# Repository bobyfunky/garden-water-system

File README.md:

# garden-water-system
Automatic water system

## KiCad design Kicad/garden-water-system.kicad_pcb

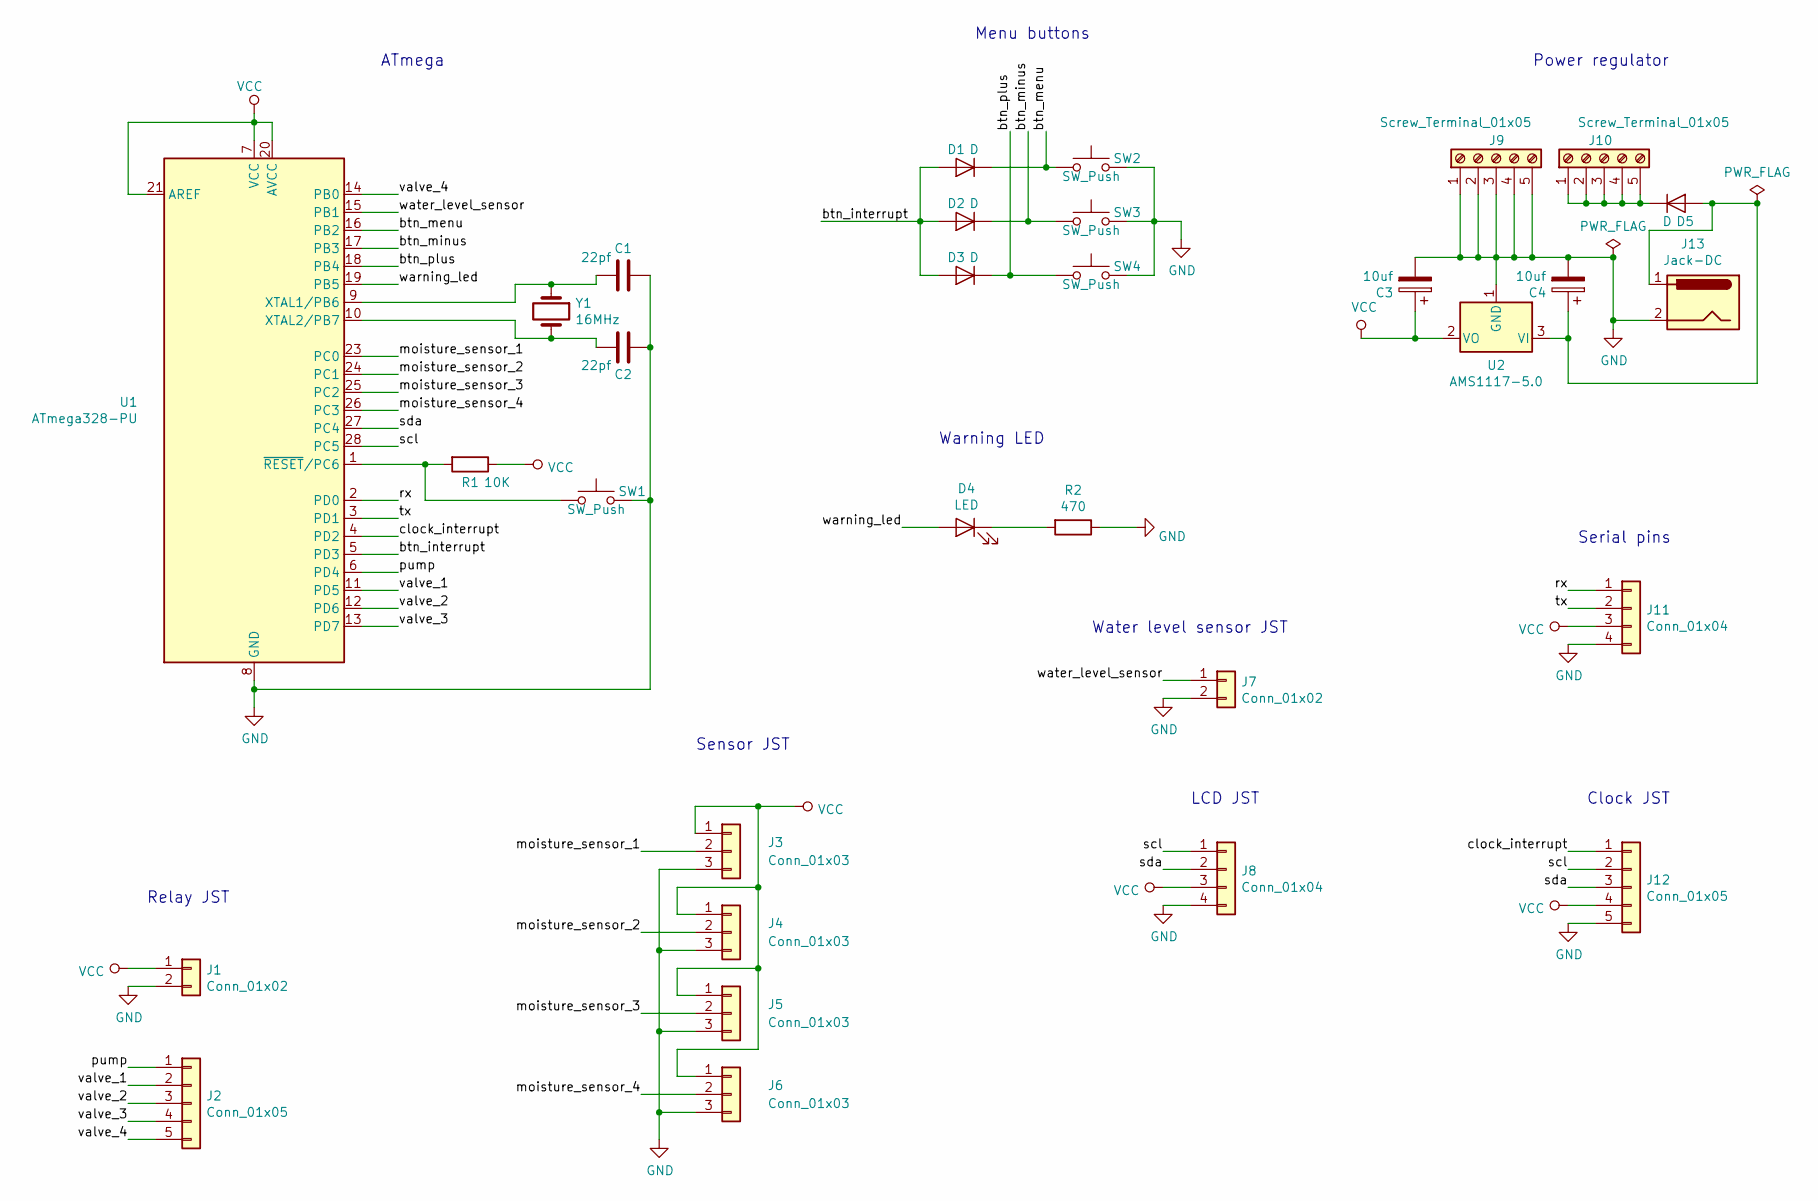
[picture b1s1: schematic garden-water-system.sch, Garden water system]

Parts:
C1, C2: 22pf; C_0805_2012Metric_Pad1.15x1.40mm_HandSolder
C3, C4: 10uf; CP_Elec_6.3x5.8
D1, D2, D3: D; D_0805_2012Metric_Pad1.15x1.40mm_HandSolder
D4: LED; LED_0805_2012Metric_Pad1.15x1.40mm_HandSolder
D5: D; D_2010_5025Metric_Pad1.52x2.65mm_HandSolder
J1, J7: Conn_01x02; JST_XH_B2B-XH-AM_1x02_P2.50mm_Vertical
J2: Conn_01x05; JST_XH_B5B-XH-AM_1x05_P2.50mm_Vertical
J3, J4, J5, J6: Conn_01x03; JST_XH_B3B-XH-A_1x03_P2.50mm_Vertical
J8: Conn_01x04; JST_XH_B4B-XH-AM_1x04_P2.50mm_Vertical
J9, J10: Screw_Terminal_01x05; TerminalBlock_bornier-5_P5.08mm
J11: Conn_01x04; PinHeader_1x04_P2.54mm_Vertical
J12: Conn_01x05; PinHeader_1x05_P2.54mm_Vertical
J13: Jack-DC; BarrelJack_Horizontal
R1: 10K; R_0805_2012Metric_Pad1.15x1.40mm_HandSolder
R2: 470; R_0805_2012Metric_Pad1.15x1.40mm_HandSolder
SW1, SW2, SW3, SW4: SW_Push; SW_Push_1P1T_NO_6x6mm_H9.5mm
U1: ATmega328-PU; DIP-28_W7.62mm_Socket_LongPads
U2: AMS1117-5.0; SOT-223-3_TabPin2
Y1: 16MHz; Crystal_SMD_SeikoEpson_MC405-2Pin_9.6x4.1mm_HandSoldering

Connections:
/btn_interrupt: D1.2 (A), D2.2 (A), D3.2 (A), U1.5 (PD3)
/btn_menu: D1.1 (K), SW2.1, U1.16 (PB2)
/btn_minus: D2.1 (K), SW3.1, U1.17 (PB3)
/btn_plus: D3.1 (K), SW4.1, U1.18 (PB4)
/clock_interrupt: J12.1, U1.4 (PD2)
/moisture_sensor_1: J3.2, U1.23 (PC0)
/moisture_sensor_2: J4.2, U1.24 (PC1)
/moisture_sensor_3: J5.2, U1.25 (PC2)
/moisture_sensor_4: J6.2, U1.26 (PC3)
/pump: J2.1, U1.6 (PD4)
/rx: J11.1, U1.2 (PD0)
/scl: J8.1, J12.2, U1.28 (PC5)
/sda: J8.2, J12.3, U1.27 (PC4)
/tx: J11.2, U1.3 (PD1)
/valve_1: J2.2, U1.11 (PD5)
/valve_2: J2.3, U1.12 (PD6)
/valve_3: J2.4, U1.13 (PD7)
/valve_4: J2.5, U1.14 (PB0)
/warning_led: D4.2 (A), U1.19 (PB5)
/water_level_sensor: J7.1, U1.15 (PB1)
GND: C1.1, C2.1, C3.2, C4.2, J1.2, J3.3, J4.3, J5.3, J6.3, J7.2, J8.4, J9.1, J9.2, J9.3, J9.4, J9.5, J11.4, J12.5, J13.2, R2.1, SW1.2, SW2.2, SW3.2, SW4.2, U1.8 (GND), U1.22 (GND), U2.1 (GND)
unnamed: C1.2, U1.9 (XTAL1/PB6), Y1.1
unnamed: C2.2, U1.10 (XTAL2/PB7), Y1.2
unnamed: C4.1, D5.2 (A), J13.1, U2.3 (VI)
unnamed: D4.1 (K), R2.2
unnamed: D5.1 (K), J10.1, J10.2, J10.3, J10.4, J10.5
unnamed: R1.2, SW1.1, U1.1 (~RESET~/PC6)
VCC: C3.1, J1.1, J3.1, J4.1, J5.1, J6.1, J8.3, J11.3, J12.4, R1.1, U1.7 (VCC), U1.20 (AVCC), U1.21 (AREF), U2.2 (VO)

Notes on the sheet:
Sensor JST
Relay JST
LCD JST
Clock JST
Serial pins
Water level sensor JST
Warning LED
Menu buttons
Power regulator
ATmega

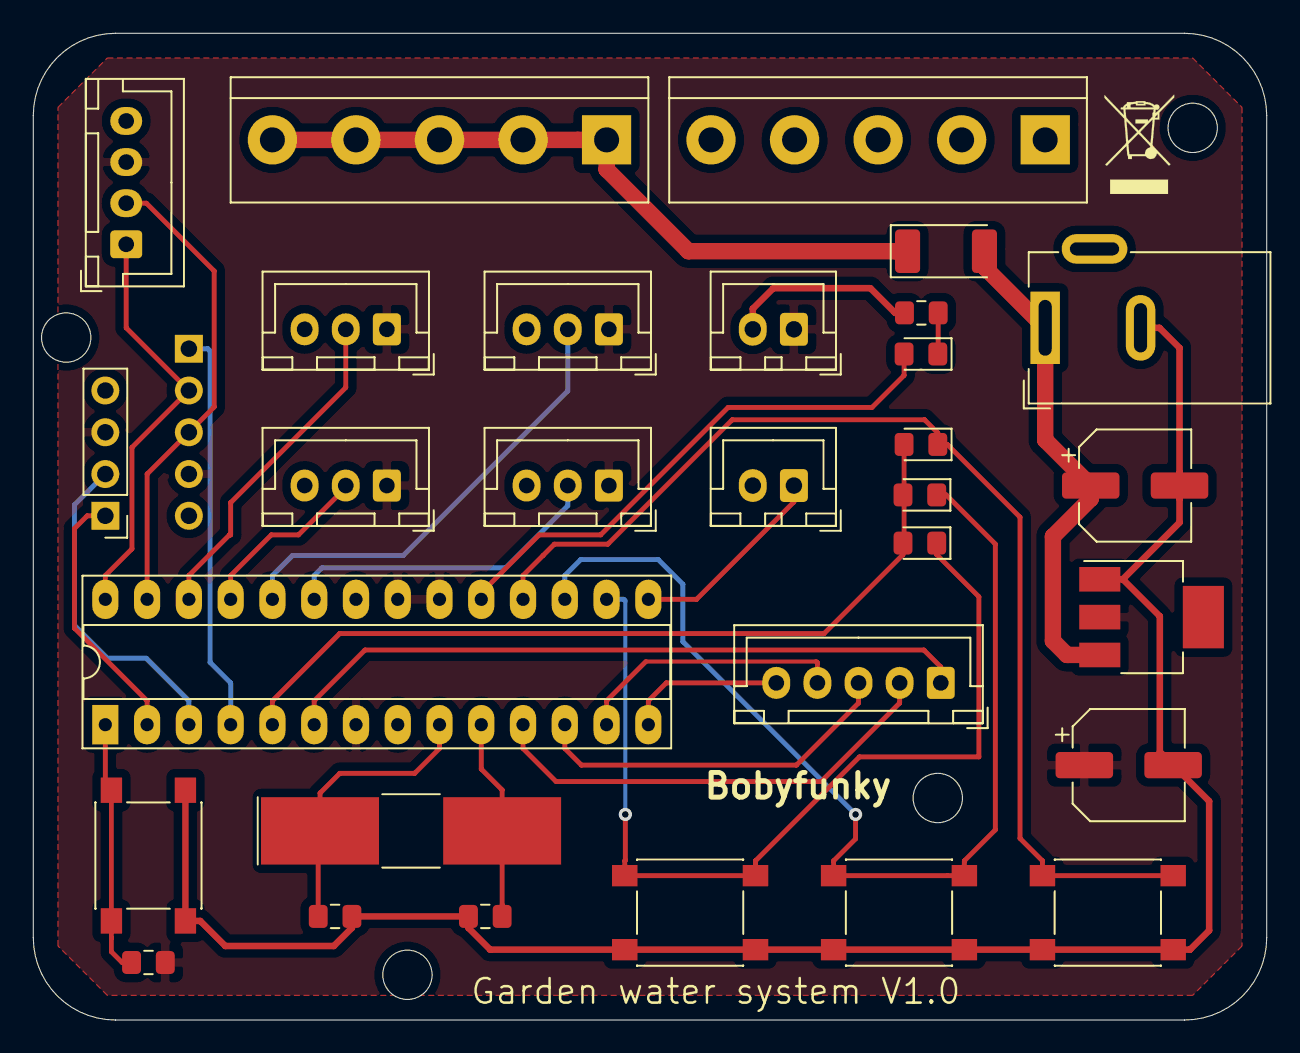
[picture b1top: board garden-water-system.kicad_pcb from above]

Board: 2 copper layers, 75.0 x 60.0 mm, 31 parts (1 on the bottom side), 28 nets.

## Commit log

2019-08-18 Init
2019-09-13 Add structure for the DS3231.
2019-10-03 add timer handler
2019-10-04 Handle the clock. Need to be tested
2019-10-17 Correction issue variable wateringStart.
2019-10-17 Correction issue of zones watering
2019-12-08 Input in pullup mode to avoid fake interrupt on noises
2019-12-16 KiCad project
2019-12-19 Gerber files + drill files
2019-12-19 Add board 3D pic
2019-12-21 Add protection diode on hardware power supply
2019-12-21 Gerber + drills files
2019-12-21 Correction pins AMS1117 5.0
2019-12-30 Update main.cpp
    HAndle waering without valve and report from master buttons with pull_up resistors.
2019-12-30 Real time data for submenu time and submenu clock (NOT TESTED)
2019-12-30 Multiples corrections
2019-12-30 Bug stopAll() before sleep
2020-03-08 Add extractor function + supp two zones
2020-03-09 Update main.cpp
    Add delay on actions + clean
2020-03-09 Add tests on sensor + init of window handler
2020-03-10 Add monitoring + offset extractor
2020-03-10 Add monitoring display
2020-03-11 Correction monitoring
2020-03-11 Add rotary encoder
